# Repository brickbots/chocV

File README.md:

# chocV

A 36 key choc keyboard based on the [Horizon](https://github.com/skarrmann/horizon) 
construction and a trimmed down [BabyV](https://www.instagram.com/eyeohdesigns/?hl=en) layout!

## Horizon + BabyV

The Horizon features a very unique and innovative construction and when I saw it, I knew 
I had to build one... but I've become really enamoured with the [Miryoku](https://github.com/manna-harbour/miryoku)
layout on my BabyV.  So I decided to mash them together and see what happens.  
Thus the chocV was born!

## Construction

[Skarrmann](https://github.com/skarrmann/horizon) has a wonderful description of 
the concept, but the main idea is to generate at least TWO pcb's for the keyboard.  One 
standard PCB with traces and all the components, and a second which bolts directly 
under with cutouts that match all the components on the first to protect them (and your 
desk) from damage.  This ends up creating a really tidy and very low profile board.

The specific footprints used and a plugin for KiCad to enable easy generation of the 
muiltiple PCB's can be found in the Horizon repo.  It's a very clever idea which is executed
exceptionally well.  All I did was re-arrange it a bit to get a layout I prefer.  I've added 
the KiCad files I generated in this repo as an example or jumping off point for others.

## Production

I used JLCPCB, as the original did, and the boards turned out great.  If you'd like to order a set of your own, the three gerber zip files are in the /gerbers folder.  You'll need one of each to
build a full board and I suggest you take a look through the Horizon repo to get a sense for 
the build process. 

I've built two complete boards, one based on the Elite-C to serve as a wired board and one 
built around a Nice:Nano for wireless functionality.  

## Keymap / Layout

The Miryoku layout is what I use across all my boards.  It's very flexible and can be 
used/implemented on just about any physical layout.  I've used it on split boards mostly, but 
when I got the BabyV I feel like I really hit a sweet spot.  Splits are great, and they do 
feel better when I do a lot of typing, but the BabyV has a great sound, good looks, and 
monoblocks are just easier to manage on a desk... it might have a few too many keys, but 
nothing is perfect :-)

Miryoku has both a fully supported QMK build system and a work in progress system for ZMK.
If you are looking for a well thought-out minimalist layout, I can't recommend it enough.

## Build one yourself!

If you are interested in building a chocV, feel free to use the files here and to reach out with
any questions.  Happy Keyboarding!

<a href='https://ko-fi.com/brickbots' target='_blank'>

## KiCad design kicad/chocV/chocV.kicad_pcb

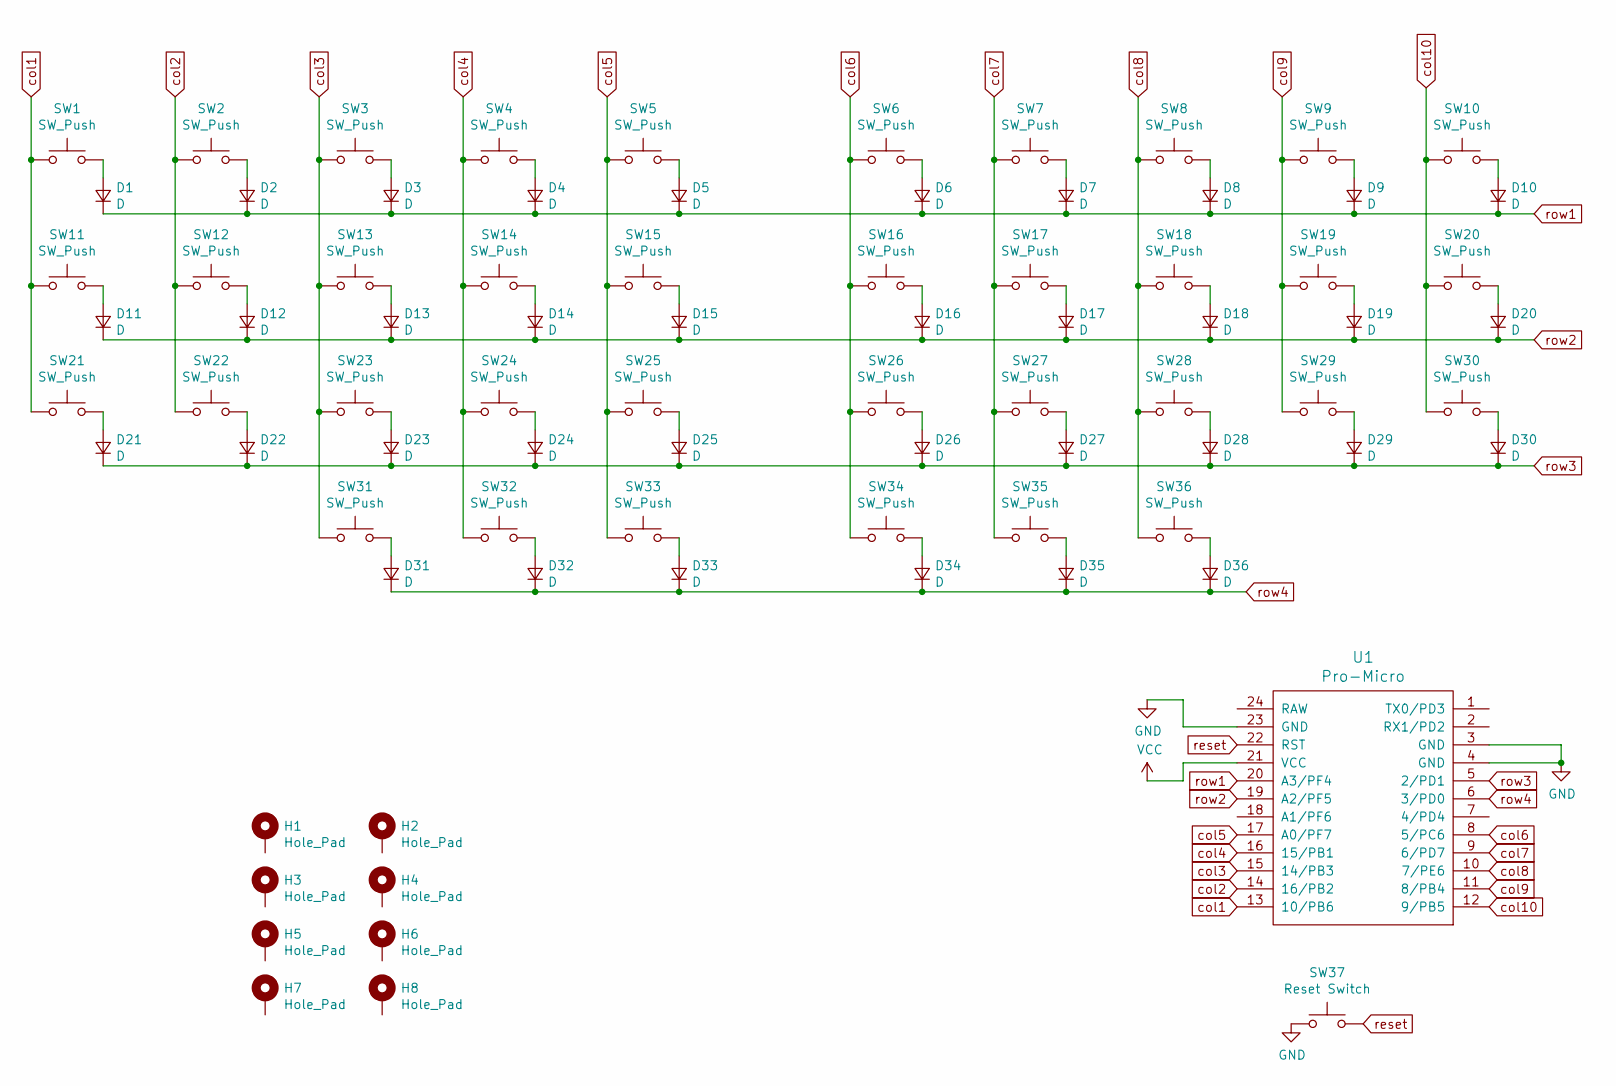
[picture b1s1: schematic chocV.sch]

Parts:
D1, D2, D3, D4, D5, D6, D7, D8, D9, D10, D11, D12, D13, D14, D15, D16, D17, D18, D19, D20, D21, D22, D23, D24, D25, D26, D27, D28, D29, D30, D31, D32, D33, D34, D35, D36: D; D_SOD-123
H1, H2, H3, H4, H5, H6, H7, H8: Hole_Pad; Mount_M2
SW1, SW2, SW3, SW4, SW5, SW6, SW7, SW8, SW9, SW10, SW11, SW12, SW13, SW14, SW15, SW16, SW17, SW18, SW19, SW20, SW21, SW22, SW23, SW24, SW25, SW26, SW27, SW28, SW29, SW30, SW31, SW32, SW33, SW34, SW35, SW36: SW_Push; SW_Choc
SW37: Reset Switch; SW_Push_6mm
U1: Pro-Micro

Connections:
GND: SW37.1, U1.3 (GND), U1.4 (GND), U1.23 (GND)
unnamed: D1.2 (A), SW1.2
unnamed: D2.2 (A), SW2.2
unnamed: D3.2 (A), SW3.2
unnamed: D4.2 (A), SW4.2
unnamed: D5.2 (A), SW5.2
unnamed: D6.2 (A), SW6.2
unnamed: D7.2 (A), SW7.2
unnamed: D8.2 (A), SW8.2
unnamed: D9.2 (A), SW9.2
unnamed: D10.2 (A), SW10.2
unnamed: D11.2 (A), SW11.2
unnamed: D12.2 (A), SW12.2
unnamed: D13.2 (A), SW13.2
unnamed: D14.2 (A), SW14.2
unnamed: D15.2 (A), SW15.2
unnamed: D16.2 (A), SW16.2
unnamed: D17.2 (A), SW17.2
unnamed: D18.2 (A), SW18.2
unnamed: D19.2 (A), SW19.2
unnamed: D20.2 (A), SW20.2
unnamed: D21.2 (A), SW21.2
unnamed: D22.2 (A), SW22.2
unnamed: D23.2 (A), SW23.2
unnamed: D24.2 (A), SW24.2
unnamed: D25.2 (A), SW25.2
unnamed: D26.2 (A), SW26.2
unnamed: D27.2 (A), SW27.2
unnamed: D28.2 (A), SW28.2
unnamed: D29.2 (A), SW29.2
unnamed: D30.2 (A), SW30.2
unnamed: D31.2 (A), SW31.2
unnamed: D32.2 (A), SW32.2
unnamed: D33.2 (A), SW33.2
unnamed: D34.2 (A), SW34.2
unnamed: D35.2 (A), SW35.2
unnamed: D36.2 (A), SW36.2
VCC: U1.21 (VCC)
col1: SW1.1, SW11.1, SW21.1, U1.13 (10/PB6)
col2: SW2.1, SW12.1, SW22.1, U1.14 (16/PB2)
col3: SW3.1, SW13.1, SW23.1, SW31.1, U1.15 (14/PB3)
col4: SW4.1, SW14.1, SW24.1, SW32.1, U1.16 (15/PB1)
col5: SW5.1, SW15.1, SW25.1, SW33.1, U1.17 (A0/PF7)
col6: SW6.1, SW16.1, SW26.1, SW34.1, U1.8 (5/PC6)
col7: SW7.1, SW17.1, SW27.1, SW35.1, U1.9 (6/PD7)
col8: SW8.1, SW18.1, SW28.1, SW36.1, U1.10 (7/PE6)
col9: SW9.1, SW19.1, SW29.1, U1.11 (8/PB4)
col10: SW10.1, SW20.1, SW30.1, U1.12 (9/PB5)
reset: SW37.2, U1.22 (RST)
row1: D1.1 (K), D2.1 (K), D3.1 (K), D4.1 (K), D5.1 (K), D6.1 (K), D7.1 (K), D8.1 (K), D9.1 (K), D10.1 (K), U1.20 (A3/PF4)
row2: D11.1 (K), D12.1 (K), D13.1 (K), D14.1 (K), D15.1 (K), D16.1 (K), D17.1 (K), D18.1 (K), D19.1 (K), D20.1 (K), U1.19 (A2/PF5)
row3: D21.1 (K), D22.1 (K), D23.1 (K), D24.1 (K), D25.1 (K), D26.1 (K), D27.1 (K), D28.1 (K), D29.1 (K), D30.1 (K), U1.5 (2/PD1)
row4: D31.1 (K), D32.1 (K), D33.1 (K), D34.1 (K), D35.1 (K), D36.1 (K), U1.6 (3/PD0)

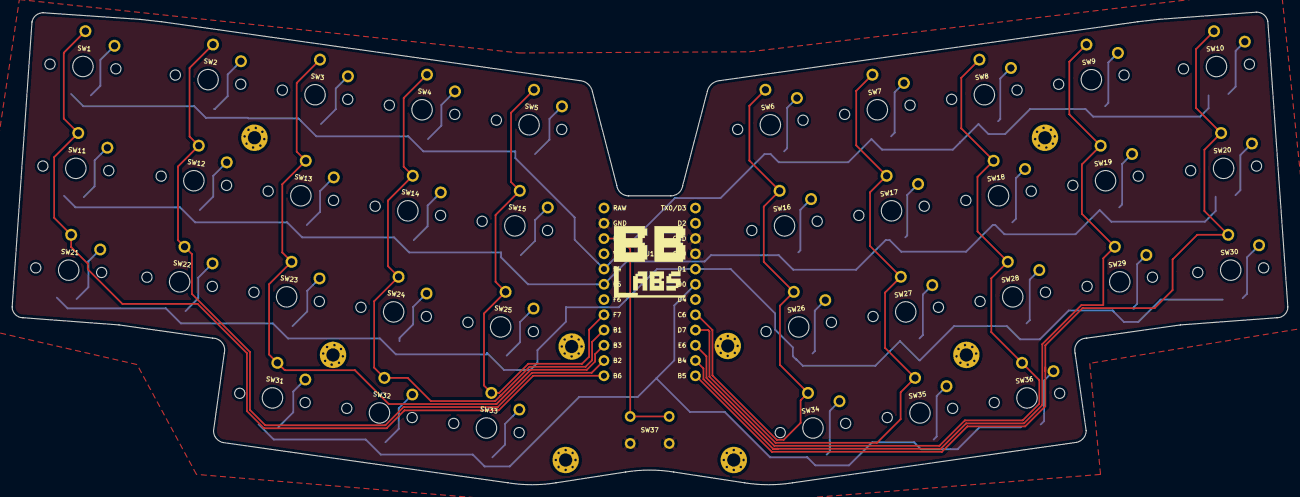
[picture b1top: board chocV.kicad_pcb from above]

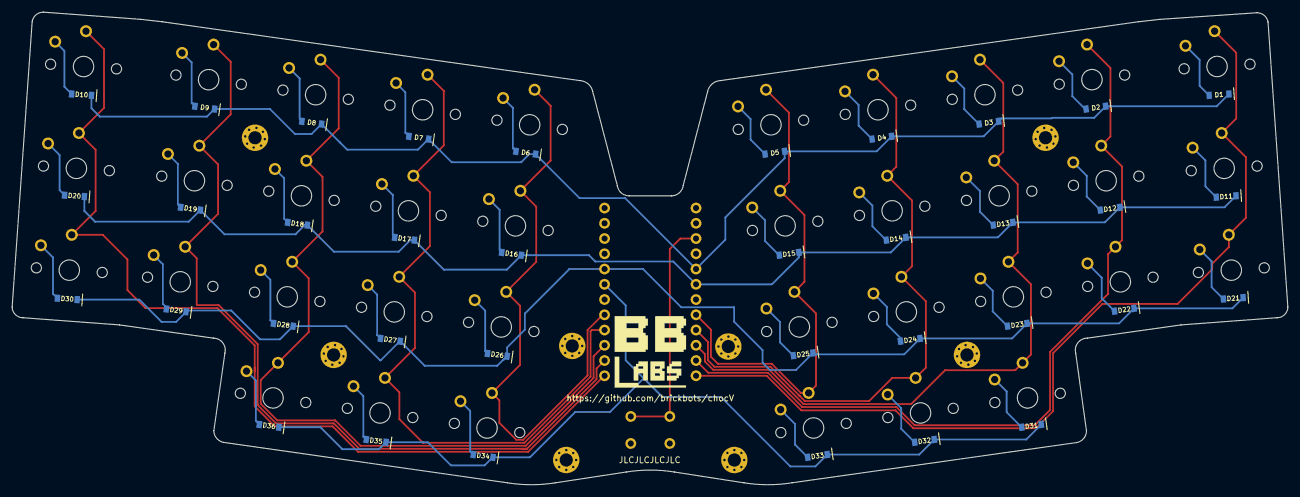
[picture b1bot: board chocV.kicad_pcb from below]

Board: 2 copper layers, 212.5 x 78.7 mm, 84 parts (37 on the bottom side), 52 nets.

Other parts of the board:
LOGO1, LOGO2: LOGO; bblabs_logo_sml

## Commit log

2021-11-14 Initial commit of board
2021-11-14 Add JLC marker for part number. Sent to fab
2021-12-14 Fleshed out readme + pics
2021-12-14 Fix readme like break
2021-12-14 Fix readme typo
2021-12-14 Adding MIT license
2021-12-22 Add shield config for ZMK
2021-12-22 Add transform to zmk config
2021-12-22 Fix up overlay syntax
2021-12-23 Add default ZMK firmware
2022-01-14 Add prebuilt QMK firmware
2022-01-19 Fix up ZMK matrix transform - Thanks dkneeland
2023-01-24 Adding funding
2023-01-24 Buy me a coffee
